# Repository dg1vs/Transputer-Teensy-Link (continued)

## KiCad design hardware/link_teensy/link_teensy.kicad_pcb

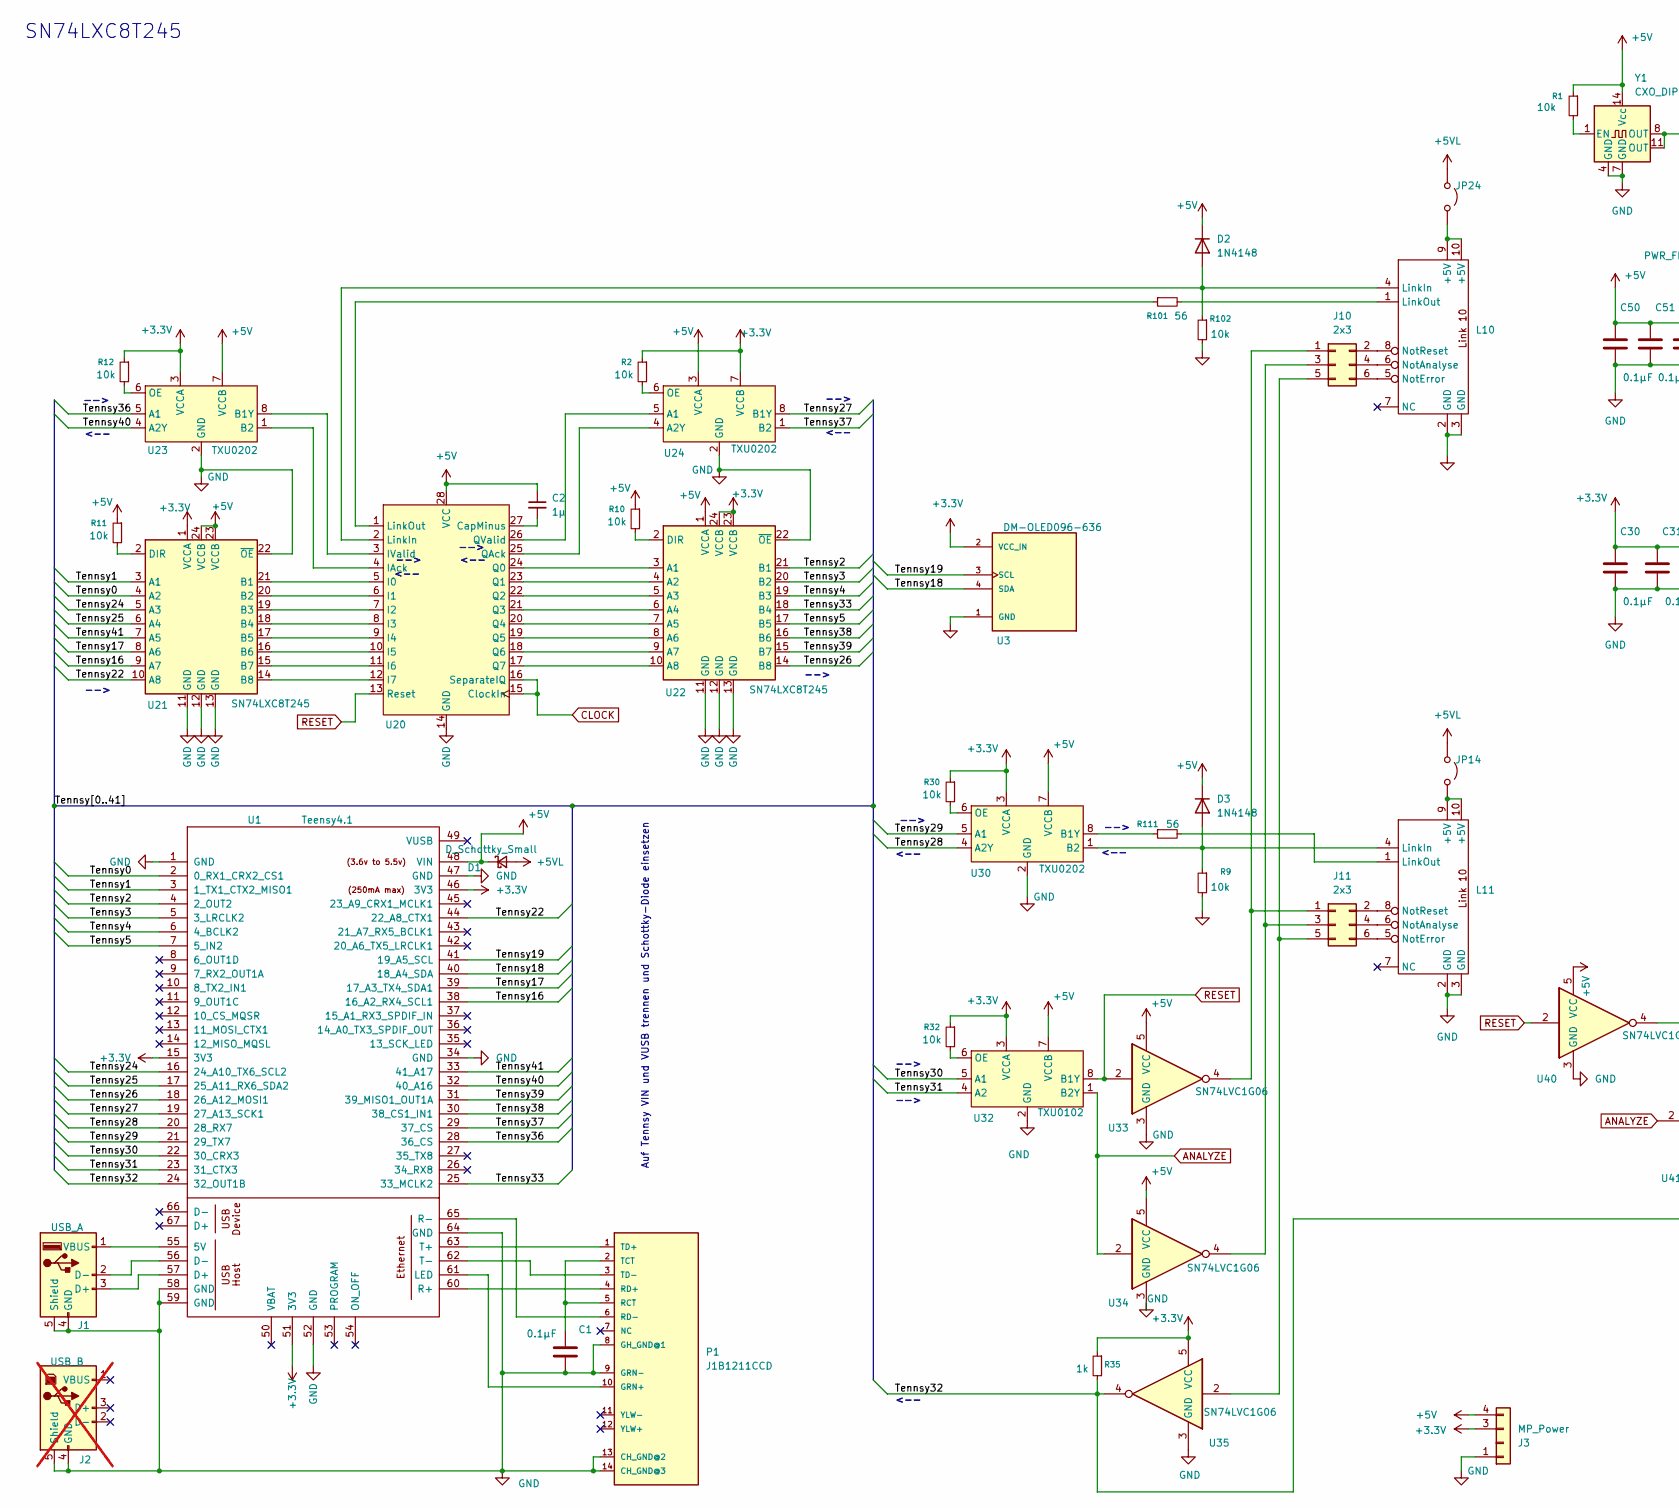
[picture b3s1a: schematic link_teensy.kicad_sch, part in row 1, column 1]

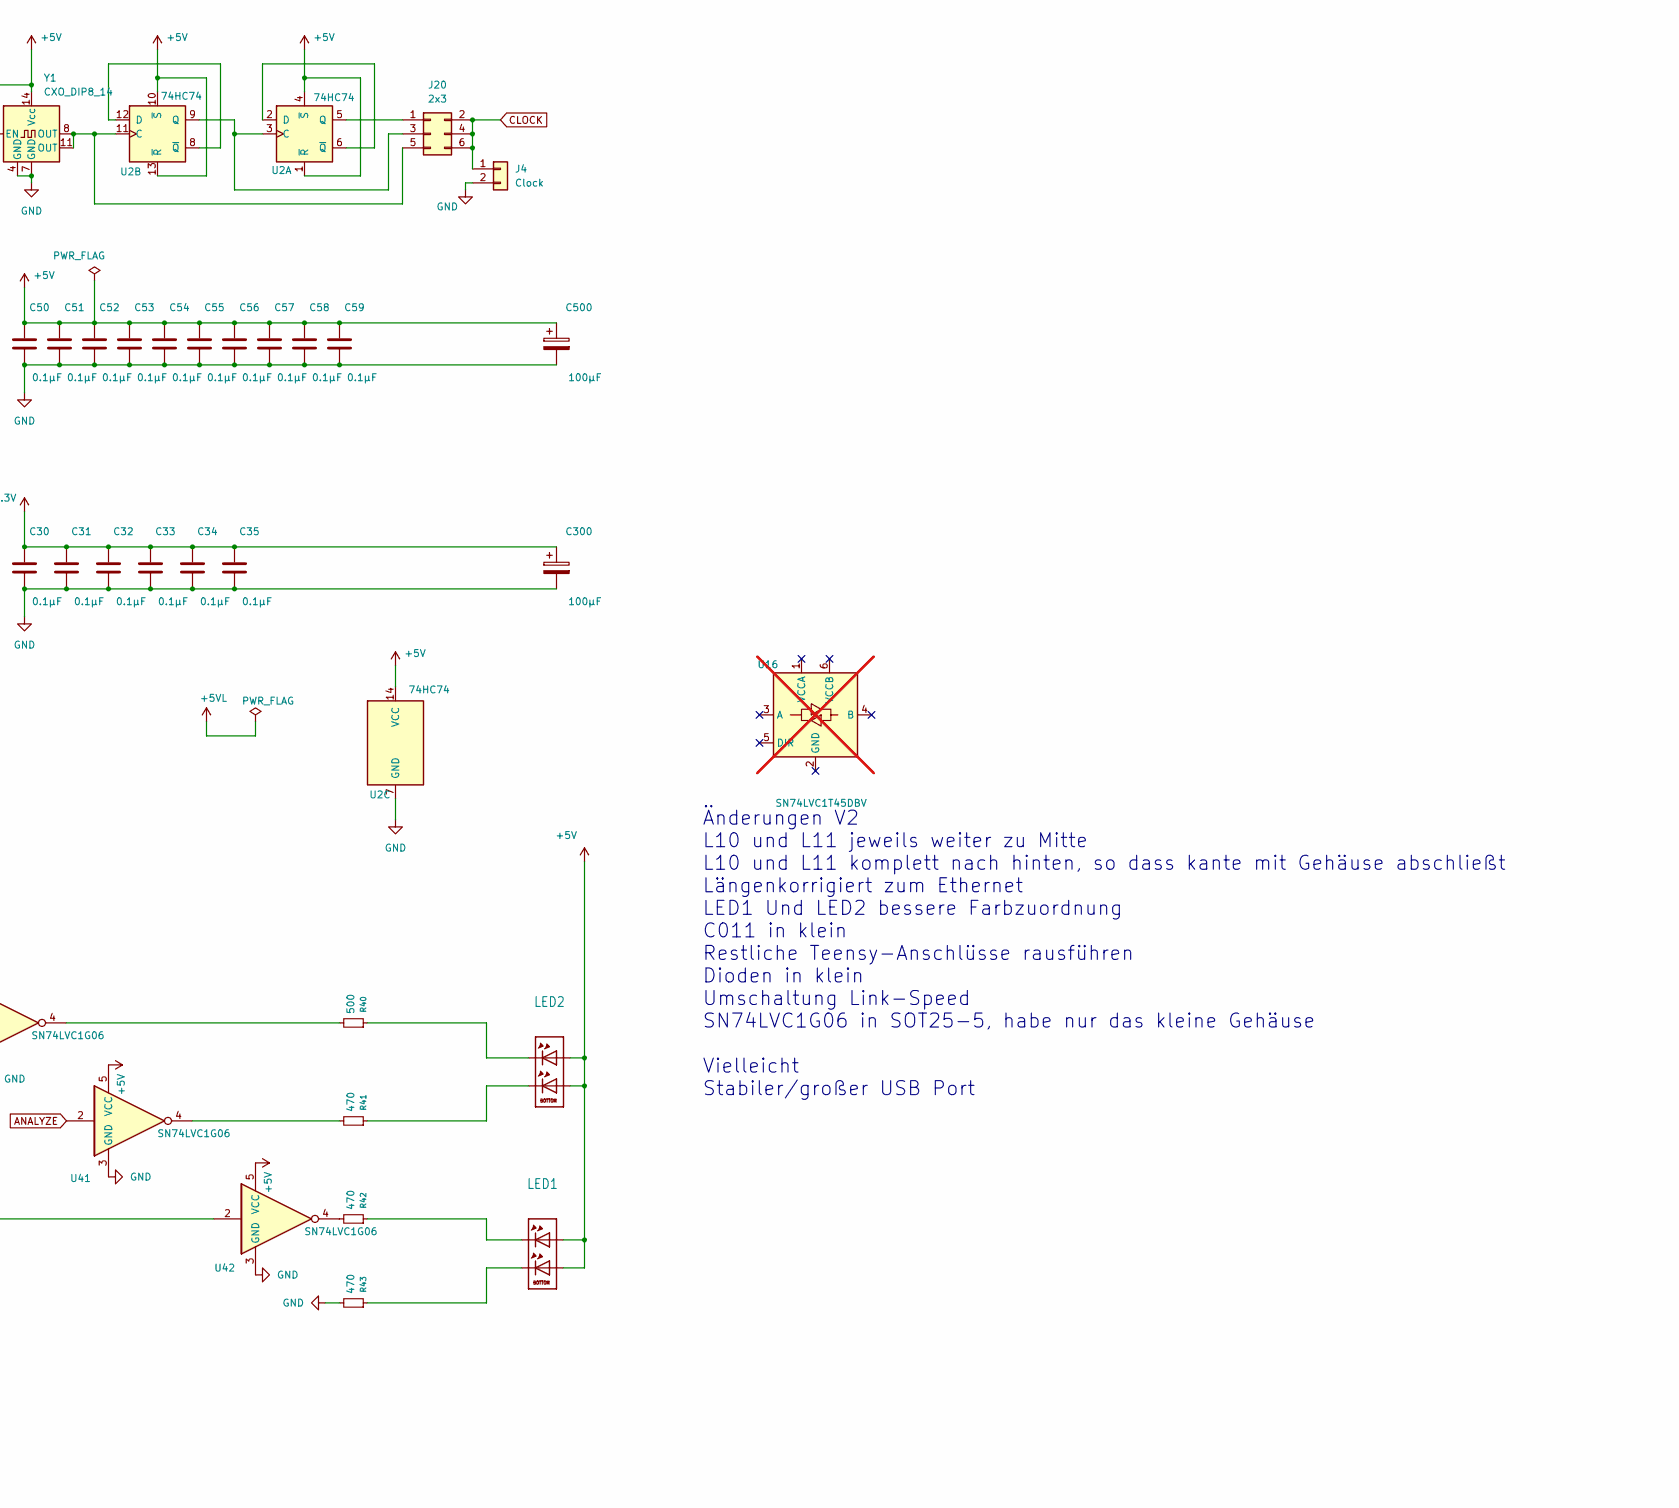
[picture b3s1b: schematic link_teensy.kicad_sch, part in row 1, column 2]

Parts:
C1, C30, C31, C32, C33, C34, C35, C50, C51, C52, C53, C54, C55, C56, C57, C58, C59: 0.1µF; C_0603_1608Metric_Pad1.08x0.95mm_HandSolder
C2: 1µ; C_1206_3216Metric_Pad1.33x1.80mm_HandSolder
C300, C500: 100µF; CP_Elec_5x3.9
D1: D_Schottky_Small; D_SMB
D2, D3: 1N4148; D_A-405_P7.62mm_Horizontal
J1: USB_A
J2: USB_B; USB_B_Lumberg_2411_02_Horizontal; not fitted
J3: MP_Power; PinHeader_1x04_P2.54mm_Vertical
J4: Clock; PinHeader_1x02_P2.54mm_Vertical
J10, J11, J20: 2x3; PinHeader_2x03_P2.54mm_Vertical
JP14, JP24: Jumper_2_Open; PinHeader_1x02_P2.54mm_Vertical
L10, L11: IDC-Header_2x05_P2.54mm_Horizontal
LED1, LED2: mentor_LED_2
P1: J1B1211CCD
R1, R2, R9, R10, R11, R12, R30, R32, R102: 10k; R_0603_1608Metric_Pad0.98x0.95mm_HandSolder
R35: 1k; R_0603_1608Metric_Pad0.98x0.95mm_HandSolder
R40: 500; R_0805_2012Metric_Pad1.20x1.40mm_HandSolder
R41, R42, R43: 470; R_0805_2012Metric_Pad1.20x1.40mm_HandSolder
R101, R111: 56; R_0603_1608Metric_Pad0.98x0.95mm_HandSolder
U1: Teensy4.1; Teensy41
U2: 74HC74; SO-14_5.3x10.2mm_P1.27mm
U3: DM-OLED096-636; MODULE_DM-OLED096-636
U16: SN74LVC1T45DBV; SOT-23-6; not fitted
U20: IMSC011Mode1; DIP-28_W15.24mm_LongPads
U21, U22: SN74LXC8T245; TSSOP-24_4.4x7.8mm_P0.65mm
U23, U24, U30: TXU0202; VSSOP-8_2.3x2mm_P0.5mm
U32: TXU0102; VSSOP-8_2.3x2mm_P0.5mm
U33, U34, U35, U40, U41, U42: SN74LVC1G06; SOT-353_SC-70-5
Y1: CXO_DIP8_14; Oscillator_DIP-8_14

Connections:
+3.3V: C30.1, C31.1, C32.1, C33.1, C34.1, C35.1, C300.1, J3.3 (Pin_4), R2.1, R12.1, R30.1, R32.1, R35.1, U1.15 (3V3), U1.46 (3V3), U1.51 (3V3), U3.2 (VCC_IN), U21.1 (VCCA), U22.23 (VCCB), U22.24 (VCCB), U23.3 (VCCA), U24.7 (VCCB), U30.3 (VCCA), U32.3 (VCCA), U35.5 (VCC)
+5V: C2.1, C50.1, C51.1, C52.1, C53.1, C54.1, C55.1, C56.1, C57.1, C58.1, C59.1, C500.1, D1.1 (K), D2.1 (K), D3.1 (K), J3.4, LED1.A1 (A2), LED1.A2, LED2.A1 (A2), LED2.A2, R1.1, R10.1, R11.1, U1.48 (VIN), U2.1 (~R), U2.4 (~S), U2.10 (~S), U2.13 (~R), U2.14 (VCC), U20.28 (VCC), U21.23 (VCCB), U21.24 (VCCB), U22.1 (VCCA), U23.7 (VCCB), U24.3 (VCCA), U30.7 (VCCB), U32.7 (VCCB), U33.5 (VCC), U34.5 (VCC), U40.5 (VCC), U41.5 (VCC), U42.5 (VCC), Y1.14 (Vcc)
+5VL: D1.2 (A), JP14.1 (A), JP24.1 (A)
/Tennsy0: U1.2 (0_RX1_CRX2_CS1), U21.4 (A2)
/Tennsy1: U1.3 (1_TX1_CTX2_MISO1), U21.3 (A1)
/Tennsy2: U1.4 (2_OUT2), U22.21 (B1)
/Tennsy3: U1.5 (3_LRCLK2), U22.20 (B2)
/Tennsy4: U1.6 (4_BCLK2), U22.19 (B3)
/Tennsy5: U1.7 (5_IN2), U22.17 (B5)
/Tennsy16: U1.38 (16_A2_RX4_SCL1), U21.9 (A7)
/Tennsy17: U1.39 (17_A3_TX4_SDA1), U21.8 (A6)
/Tennsy18: U1.40 (18_A4_SDA), U3.4 (SDA)
/Tennsy19: U1.41 (19_A5_SCL), U3.3 (SCL)
/Tennsy22: U1.44 (22_A8_CTX1), U21.10 (A8)
/Tennsy24: U1.16 (24_A10_TX6_SCL2), U21.5 (A3)
/Tennsy25: U1.17 (25_A11_RX6_SDA2), U21.6 (A4)
/Tennsy26: U1.18 (26_A12_MOSI1), U22.14 (B8)
/Tennsy27: U1.19 (27_A13_SCK1), U24.8 (B1Y)
/Tennsy28: U1.20 (28_RX7), U30.4 (A2Y)
/Tennsy29: U1.21 (29_TX7), U30.5 (A1)
/Tennsy30: U1.22 (30_CRX3), U32.5 (A1)
/Tennsy31: U1.23 (31_CTX3), U32.4 (A2)
/Tennsy32: R35.2, U1.24 (32_OUT1B), U35.4, U42.2
/Tennsy33: U1.25 (33_MCLK2), U22.18 (B4)
/Tennsy36: U1.28 (36_CS), U23.5 (A1)
/Tennsy37: U1.29 (37_CS), U24.1 (B2)
/Tennsy38: U1.30 (38_CS1_IN1), U22.16 (B6)
/Tennsy39: U1.31 (39_MISO1_OUT1A), U22.15 (B7)
/Tennsy40: U1.32 (40_A16), U23.4 (A2Y)
/Tennsy41: U1.33 (41_A17), U21.7 (A5)
ANALYZE: U32.1 (B2Y), U34.2, U41.2
CLOCK: J4.1, J20.2, J20.4, J20.6, U20.15 (ClockIn), U20.16 (SeparateIQ)
GND: C1.2, C30.2, C31.2, C32.2, C33.2, C34.2, C35.2, C50.2, C51.2, C52.2, C53.2, C54.2, C55.2, C56.2, C57.2, C58.2, C59.2, C300.2, C500.2, J1.4 (GND), J1.5 (Shield), J2.4 (GND), J2.5 (Shield), J3.1, J4.2, L10.2 (GND), L10.3 (GND), L11.2 (GND), L11.3 (GND), P1.8 (GH_GND@1), P1.9 (GRN-), P1.13 (CH_GND@2), P1.14 (CH_GND@3), R9.2, R43.2, R102.2, U1.1 (GND), U1.34 (GND), U1.47 (GND), U1.52 (GND), U1.58 (GND), U1.59 (GND), U1.64 (GND), U2.7 (GND), U3.1 (GND), U20.14 (GND), U21.11 (GND), U21.12 (GND), U21.13 (GND), U21.22 (~OE), U22.11 (GND), U22.12 (GND), U22.13 (GND), U22.22 (~OE), U23.2 (GND), U24.2 (GND), U30.2 (GND), U32.2 (GND), U33.3 (GND), U34.3 (GND), U35.3 (GND), U40.3 (GND), U41.3 (GND), U42.3 (GND), Y1.4 (GND), Y1.7 (GND)
unnamed: D2.2 (A), L10.4 (LinkIn), R102.1, U20.2 (LinkIn)
unnamed: D3.2 (A), L11.4 (LinkIn), R9.1, U30.1 (B2)
unnamed: J1.3 (D+), U1.57 (D+)
unnamed: J1.2 (D-), U1.56 (D-)
unnamed: J1.1 (VBUS), U1.55 (5V)
unnamed: J10.1, J11.1, U33.4
unnamed: J10.2, L10.8 (NotReset)
unnamed: J10.3, J11.3, U34.4
unnamed: J10.4, L10.6 (NotAnalyse)
unnamed: J10.5, J11.5, U35.2
unnamed: J10.6, L10.5 (NotError)
unnamed: J11.2, L11.8 (NotReset)
unnamed: J11.4, L11.6 (NotAnalyse)
unnamed: J11.6, L11.5 (NotError)
unnamed: J20.1, U2.5 (Q)
unnamed: J20.3, U2.3 (C), U2.9 (Q)
unnamed: J20.5, U2.11 (C), Y1.8 (OUT), Y1.11 (OUT)
unnamed: JP14.2 (B), L11.9 (+5V), L11.10 (+5V)
unnamed: JP24.2 (B), L10.9 (+5V), L10.10 (+5V)
unnamed: L10.1 (LinkOut), R101.2
unnamed: L11.1 (LinkOut), R111.2
unnamed: LED1.C1, R43.1
unnamed: LED1.C2, R42.1
unnamed: LED2.C1, R41.1
unnamed: LED2.C2, R40.1
unnamed: P1.10 (GRN+), U1.61 (LED)
unnamed: C1.1, P1.2 (TCT), P1.5 (RCT)
unnamed: P1.4 (RD+), U1.60 (R+)
unnamed: P1.6 (RD-), U1.65 (R-)
unnamed: P1.1 (TD+), U1.63 (T+)
unnamed: P1.3 (TD-), U1.62 (T-)
unnamed: R40.2, U40.4
unnamed: R41.2, U41.4
unnamed: R42.2, U42.4
unnamed: U2.2 (D), U2.6 (~Q)
unnamed: U2.8 (~Q), U2.12 (D)
unnamed: C2.2, U20.27 (CapMinus)
unnamed: U20.5 (I0), U21.21 (B1)
unnamed: U20.6 (I1), U21.20 (B2)
unnamed: U20.7 (I2), U21.19 (B3)
unnamed: U20.8 (I3), U21.18 (B4)
unnamed: U20.9 (I4), U21.17 (B5)
unnamed: U20.10 (I5), U21.16 (B6)
unnamed: U20.11 (I6), U21.15 (B7)
unnamed: U20.12 (I7), U21.14 (B8)
unnamed: U20.4 (IAck), U23.1 (B2)
unnamed: U20.3 (IValid), U23.8 (B1Y)
unnamed: R101.1, U20.1 (LinkOut)
unnamed: U20.24 (Q0), U22.3 (A1)
unnamed: U20.23 (Q1), U22.4 (A2)
unnamed: U20.22 (Q2), U22.5 (A3)
unnamed: U20.21 (Q3), U22.6 (A4)
unnamed: U20.20 (Q4), U22.7 (A5)
unnamed: U20.19 (Q5), U22.8 (A6)
unnamed: U20.18 (Q6), U22.9 (A7)
unnamed: U20.17 (Q7), U22.10 (A8)
unnamed: U20.25 (QAck), U24.4 (A2Y)
unnamed: U20.26 (QValid), U24.5 (A1)
unnamed: R11.2, U21.2 (DIR)
unnamed: R10.2, U22.2 (DIR)
unnamed: R12.2, U23.6 (OE)
unnamed: R2.2, U24.6 (OE)
unnamed: R111.1, U30.8 (B1Y)
unnamed: R30.2, U30.6 (OE)
unnamed: R32.2, U32.6 (OE)
unnamed: R1.2, Y1.1 (EN)
RESET: U20.13 (Reset), U32.8 (B1Y), U33.2, U40.2

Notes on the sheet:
Auf Tennsy VIN und VUSB trennen und Schottky-Diode einsetzen
-->
Änderungen V2 L10 und L11 jeweils weiter zu Mitte L10 und L11 komplett nach hinten, so dass kante mit Gehäuse abschließt Längenkorrigiert zum Ethernet LED1 Und LED2 bessere Farbzuordnung C011 in klein Restliche Teensy-Anschlüsse rausführen Dioden in klein Umschaltung Link-Speed SN74LVC1G06 in SOT25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
<--
SN74LXC8T245

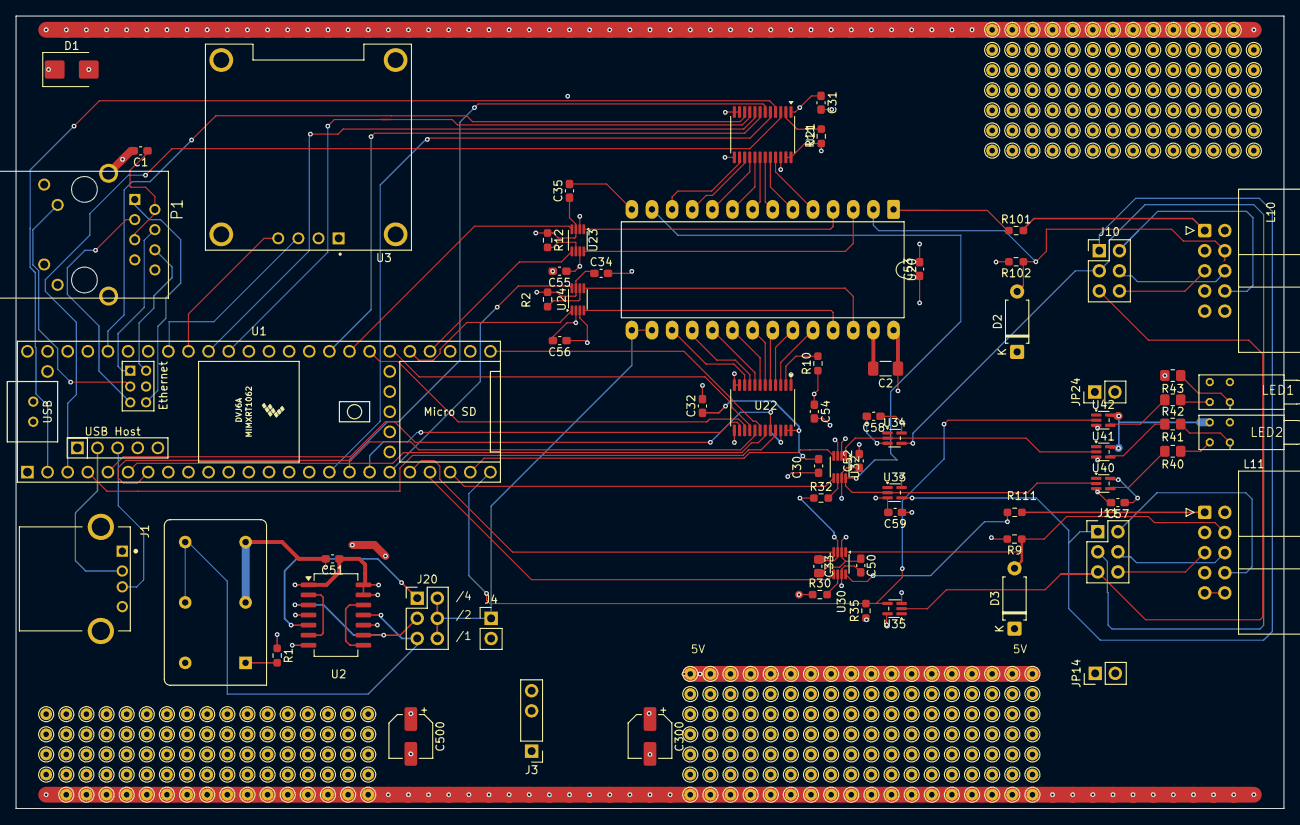
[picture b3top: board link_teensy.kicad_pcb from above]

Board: 4 copper layers, 160.0 x 100.0 mm, 69 parts (0 on the bottom side), 100 nets.

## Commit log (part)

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2026-04-11 directory structure
2026-04-11 Readme
2026-04-17 added firmware, v3 from andre
2026-04-18 start fpga adapter
2026-04-18 Add Transputer-Kicad-Library as submodule
2026-04-18 Link to submodule
2026-04-18 programm for pin test
2026-05-11 Test rev ${VCSSHORTHASH}
